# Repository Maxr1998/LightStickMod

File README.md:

# Light Stick Mod

Modding the LOOΠΔ light stick with a custom PCB/firmware, rechargeable battery and a companion Android app for wireless control.

## [pcb](pcb)

Designed in KiCAD, manufactured by JLCPCB. Uses the ESP32 as a controller.

## [firmware](firmware)

Built with [esphome.io](https://esphome.io).
Supports WiFi control, integrates with Home Assistant, introduces [animated effects](https://gfycat.com/grandcharminghogget).  
Thanks to deep sleep support, idle battery drain can be kept to a minimum.

## [app](app)

Companion app for Android to allow wireless control via Bluetooth LE. Written in Kotlin, using JetPack Compose for the UI.

## [build log](build-log.md)

Write-up on how I modded it.

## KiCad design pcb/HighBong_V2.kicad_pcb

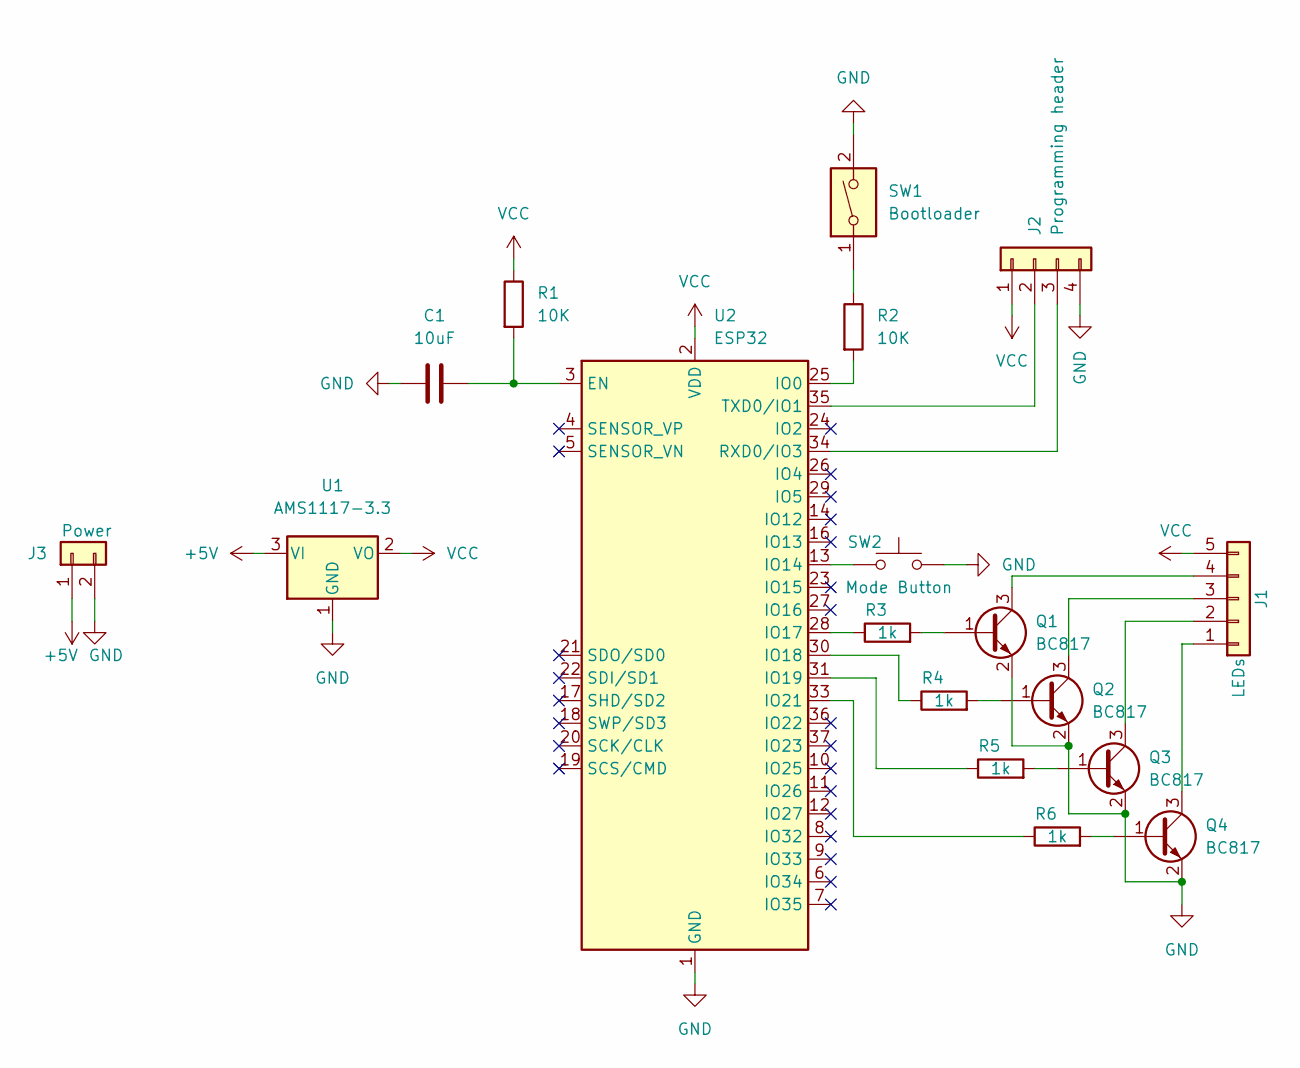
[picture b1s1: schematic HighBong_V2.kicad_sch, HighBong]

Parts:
C1: 10uF; C_0805_2012Metric_Pad1.18x1.45mm_HandSolder
J1: LEDs; JST_PH_B5B-PH-SM4-TB_1x05-1MP_P2.00mm_Vertical
J2: Programming header; PinHeader_1x04_P2.54mm_Vertical
J3: Power; JST_PH_B2B-PH-SM4-TB_1x02-1MP_P2.00mm_Vertical
Q1, Q2, Q3, Q4: BC817; SOT-23
R1, R2: 10K; R_0805_2012Metric_Pad1.20x1.40mm_HandSolder
R3, R4, R5, R6: 1k; R_0805_2012Metric_Pad1.20x1.40mm_HandSolder
SW1: Bootloader; KPS-1290
SW2: Mode Button; SW_Push_1P1T_NO_6x6mm_H9.5mm
U1: AMS1117-3.3; SOT-223-3_TabPin2
U2: ESP32; ESP32-WROOM-32

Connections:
+5V: J3.1, U1.3 (VI)
GND: C1.2, J2.4, J3.2, Q1.2 (E), Q2.2 (E), Q3.2 (E), Q4.2 (E), SW1.2, SW2.2, U1.1 (GND), U2.1 (GND), U2.15 (GND), U2.38 (GND), U2.39 (GND)
unnamed: C1.1, R1.2, U2.3 (EN)
unnamed: J1.1, Q4.3 (C)
unnamed: J1.2, Q3.3 (C)
unnamed: J1.3, Q2.3 (C)
unnamed: J1.4, Q1.3 (C)
unnamed: J2.2, U2.35 (TXD0/IO1)
unnamed: J2.3, U2.34 (RXD0/IO3)
unnamed: Q1.1 (B), R3.2
unnamed: Q2.1 (B), R4.2
unnamed: Q3.1 (B), R5.2
unnamed: Q4.1 (B), R6.2
unnamed: R2.1, SW1.1
unnamed: R2.2, U2.25 (IO0)
unnamed: R3.1, U2.28 (IO17)
unnamed: R4.1, U2.30 (IO18)
unnamed: R5.1, U2.31 (IO19)
unnamed: R6.1, U2.33 (IO21)
unnamed: SW2.1, U2.13 (IO14)
VCC: J1.5, J2.1, R1.1, U1.2 (VO), U2.2 (VDD)

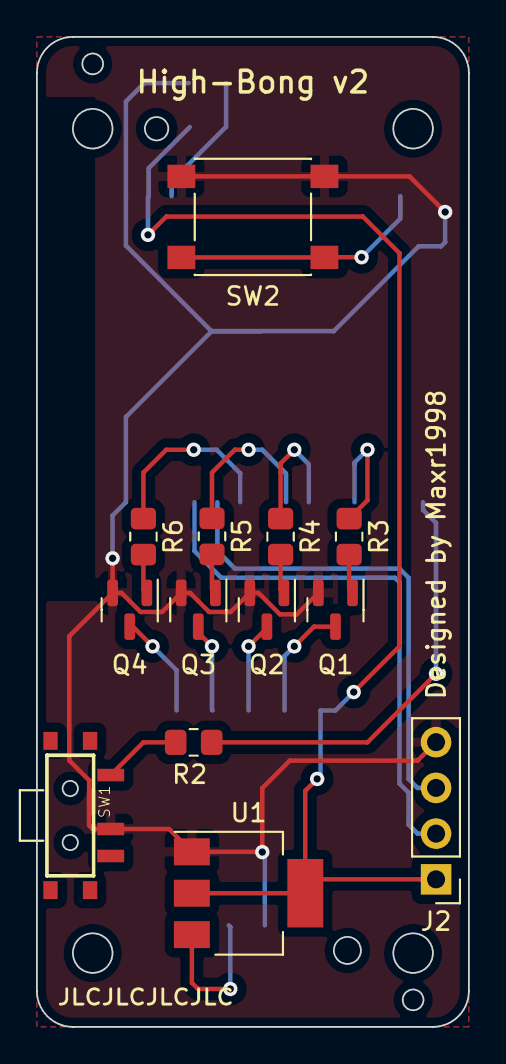
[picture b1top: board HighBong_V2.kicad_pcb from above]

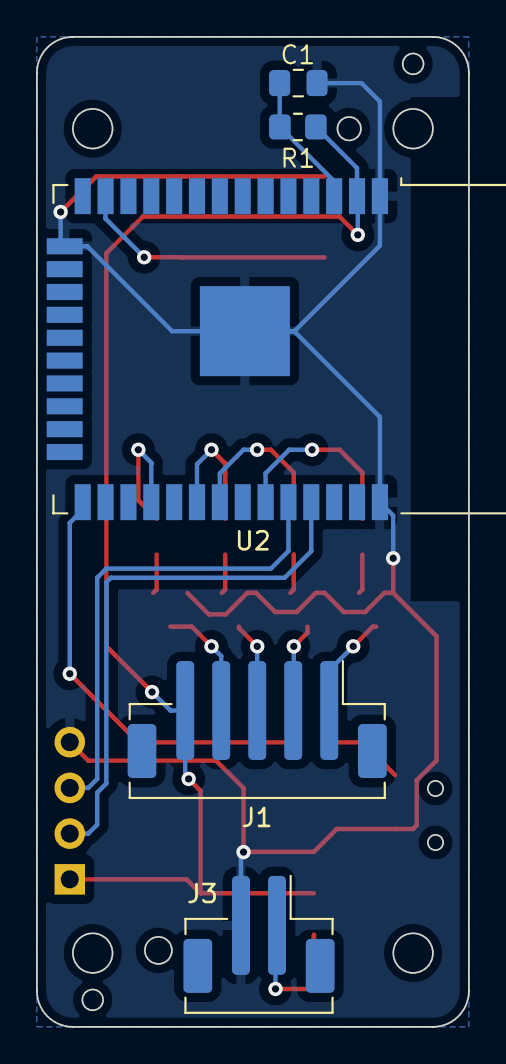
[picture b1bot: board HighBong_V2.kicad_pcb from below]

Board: 2 copper layers, 24.0 x 55.0 mm, 18 parts (5 on the bottom side), 21 nets.

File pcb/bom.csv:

Comment,Designator,Footprint,LCSC Part Number
10K,"R1,R2",0805,C17414
1K,"R3,R4,R5,R6",0805,C17513
10uF,C1,0805,C32635
BC817,"Q1,Q2,Q3,Q4",SOT-23-3,C126908
AMS1117,U1,SOT-223,C6186
ESP32,U2,SMD38,C701342
Slide Switch,SW1,SMD,C431541
6x6x5mm Tactile Switch,SW2,SMD,C782827
JST PH1 2mm Connector 5 Pin,J1,CONN-SMD,C146056

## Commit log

2022-05-11 Initial
2022-05-21 Fix issues with drill holes and swtich footprint
2022-05-21 Regenerate gerber files
2022-05-22 Move button to GPIO14
2022-06-28 Implement basic firmware
2022-07-29 Add .editorconfig
2022-07-29 Rework rainbow animations
    Using a lookup table for HSV to RGB conversion
2022-07-29 Fix click handling, add logging
2022-07-29 Add README
2022-07-31 Setup CMake project
2022-07-31 Implement bluetooth component
2022-08-17 Add breathing effect
2022-08-17 Reformat colors code
2022-08-17 Set brightness in rainbow effect
2022-08-17 Refactor colors and move global variable to static variable
2022-08-17 Don't reset effect for colors when in breathing mode
2022-08-19 Write build log
2022-08-19 Add buildscript
2022-08-19 Fix linter warnings
2022-08-19 Support setting effect via bluetooth
2022-08-19 Restore full brightness when disabling effects
2022-08-19 Create controller app scaffold
2022-08-21 Implement first iteration of controller app
2022-09-16 Add companion app to README and reword description
